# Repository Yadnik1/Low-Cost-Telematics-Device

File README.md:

# Low-Cost Telematics Device for Motor Vehicle Usage-Based Applications

## Overview
This repository details the development of a low-cost telematics device aimed at revolutionizing the motor vehicle insurance sector in India. The device captures critical vehicle kinematics and dynamics data, enabling "pay as you drive" (PAYD) and "pay how you drive" (PHYD) insurance policies. This project addresses the gap in the Indian market for an affordable, after-sales telematics device to assist insurance companies in offering more personalized services.

## Problem Statement
In India, the lack of differentiated underwriting for vehicle insurance fails to consider individual driving patterns and vehicle usage. With over 210 million registered vehicles, the opportunity to tailor insurance policies to driving behavior represents a significant untapped market. This device aims to incentivize safer driving and provide accurate data to support insurance claims and reduce fraud.

## Power Management
The telematics device is powered via a car charger and carefully manages power to support the Raspberry Pi Pico and various sensors. A specialized LDO IC (AZ1117CD) ensures stable voltage for optimal component performance.

#### Power Management Flowchart

## Interfacing Components
Components such as an OLED display, 6DOF IMU, GPS module, and environmental sensors interface with the microcontroller, providing real-time data logging on vehicle behavior and environmental conditions.

#### Interfacing Components Flowchart

#### Components Selection and Planning

## Data Storage
Data is logged onto a micro SD card in CSV format, allowing for extensive data analysis and application in developing insurance models.

# Development

### Documentation and Project Planning
All the project planning was done from ground up and all the documentaion of the project can be seen in the [Documentation folder](Documentation/).

### Component Selection
The component selection for the project was done by benchmarking the STEVAL-STWINKT1B industrial node with the VBOX IMU in real world conditions.
#### Benchmarking setup 

Additional indoor tests were also done by making a setup by laser cutting an acryclic sheet and mounting 5 industrial nodes on it to understand the sensor Systematic Errors and Random Errors in the sensors.

#### Setup to study Variability in sensors

### Designing Breakout boards and Printed Circuit Boards

1) The project involved the use of AECQ100 grade IMU and Temperature and Humidity sensors (SHT30A)  sensors for which custom breakout boards had to be created in KiCAD and hold soldered:
#### Breakout Board PCB of AEC-Q100 compliant SHT-30A Temperature and Humidity Sensor

#### Breakout Board PCB of AEC-Q100 compliant 6-DOF IMU ASM330LHHXTR

#### Fabricated Breakout Boards with IC

2) The PCB of the device was a 2 layered PCB developed using KiCAD consisting of the sensor subsytem on the top layer and power circuitry at the bottom:
#### PCB of Low cost Telematics device

### Developing firmware:

The firmware for the device was written by using the Raspberry Pi Pico as the Microcontroller in C.
The individual C code of the components as well as the entire systems firmware along with the CMake files can be seen in the [Firmware folder](Firmware/).

#### Firmware Development and Validation 

After retreiving the data from the device, errors and noise have to be addressed, for which there is a [seperate repository](https://github.com/Yadnik1/MEMS-IMU-noise-analysis/tree/master) where I have mentioned the different methodologies and filers used in Python for the post-processing process. 

## Usage
To operate the device:
1. Connect to the vehicle's power source.
2. Interact with the OLED display for instructions and status.
3. Retrieve and analyze data from the SD card as needed.

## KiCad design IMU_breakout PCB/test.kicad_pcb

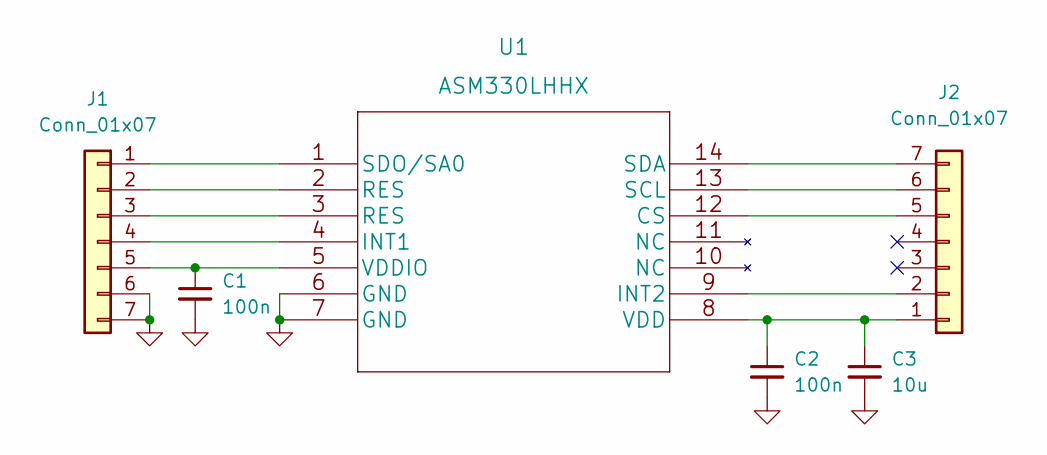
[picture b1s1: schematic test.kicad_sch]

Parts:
C1, C2: 100n; C_0805_2012Metric_Pad1.18x1.45mm_HandSolder
C3: 10u; C_0805_2012Metric_Pad1.18x1.45mm_HandSolder
J1, J2: Conn_01x07; PinHeader_1x07_P2.54mm_Vertical
U1: ASM330LHHX

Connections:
GND: C1.2, C2.2, C3.2, J1.6, J1.7, U1.6 (GND), U1.7 (GND)
unnamed: C2.1, C3.1, J2.1, U1.8 (VDD)
unnamed: J1.1, U1.1 (SDO/SA0)
unnamed: J1.2, U1.2 (RES)
unnamed: J1.3, U1.3 (RES)
unnamed: J1.4, U1.4 (INT1)
unnamed: C1.1, J1.5, U1.5 (VDDIO)
unnamed: J2.2, U1.9 (INT2)
unnamed: J2.5, U1.12 (CS)
unnamed: J2.6, U1.13 (SCL)
unnamed: J2.7, U1.14 (SDA)

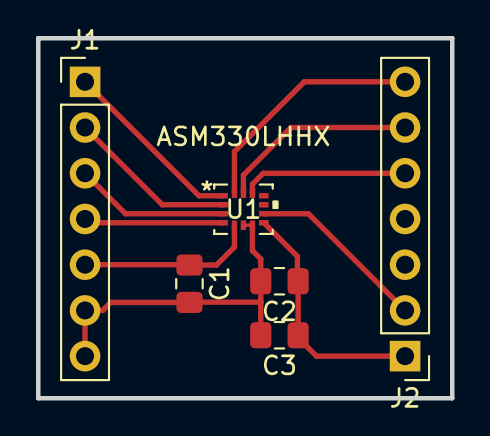
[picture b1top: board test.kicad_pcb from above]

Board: 2 copper layers, 23.0 x 20.0 mm, 6 parts (0 on the bottom side), 11 nets.

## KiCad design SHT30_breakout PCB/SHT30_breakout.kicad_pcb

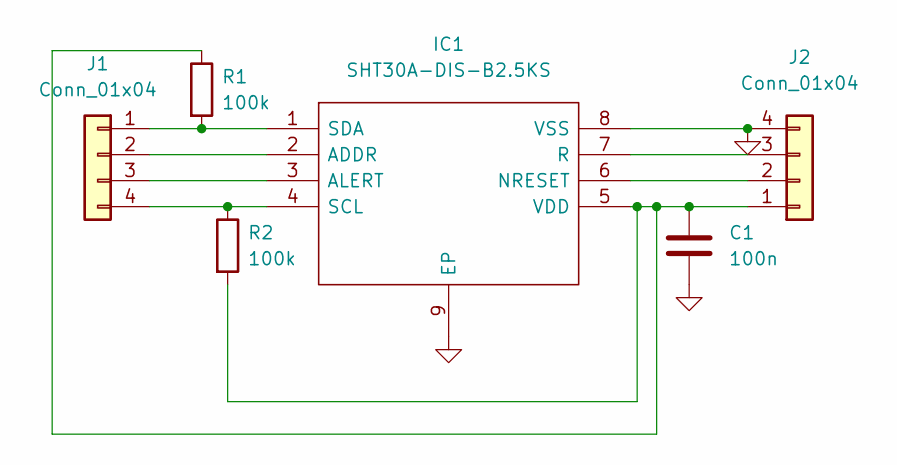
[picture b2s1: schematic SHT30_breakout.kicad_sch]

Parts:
C1: 100n; C_0805_2012Metric_Pad1.18x1.45mm_HandSolder
IC1: SHT30A-DIS-B2.5KS; SON50P250X250X100-9N-D; Manufacturer_Part_Number SHT30A-DIS-B2.5KS; Mouser Part Number 403-SHT30ADIS-B2.5KS
J1, J2: Conn_01x04; PinHeader_1x04_P2.54mm_Vertical
R1, R2: 100k; R_1206_3216Metric_Pad1.30x1.75mm_HandSolder

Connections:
GND: C1.2, IC1.8 (VSS), IC1.9 (EP), J2.4
unnamed: C1.1, IC1.5 (VDD), J2.1, R1.1, R2.2
unnamed: IC1.1 (SDA), J1.1, R1.2
unnamed: IC1.2 (ADDR), J1.2
unnamed: IC1.4 (SCL), J1.4, R2.1
unnamed: IC1.3 (ALERT), J1.3
unnamed: IC1.6 (NRESET), J2.2
unnamed: IC1.7 (R), J2.3

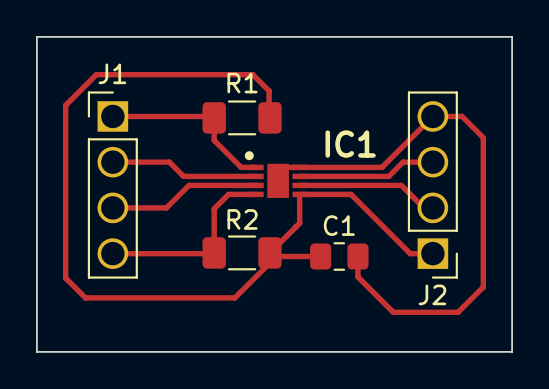
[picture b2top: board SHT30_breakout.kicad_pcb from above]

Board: 2 copper layers, 26.4 x 17.5 mm, 6 parts (0 on the bottom side), 8 nets.

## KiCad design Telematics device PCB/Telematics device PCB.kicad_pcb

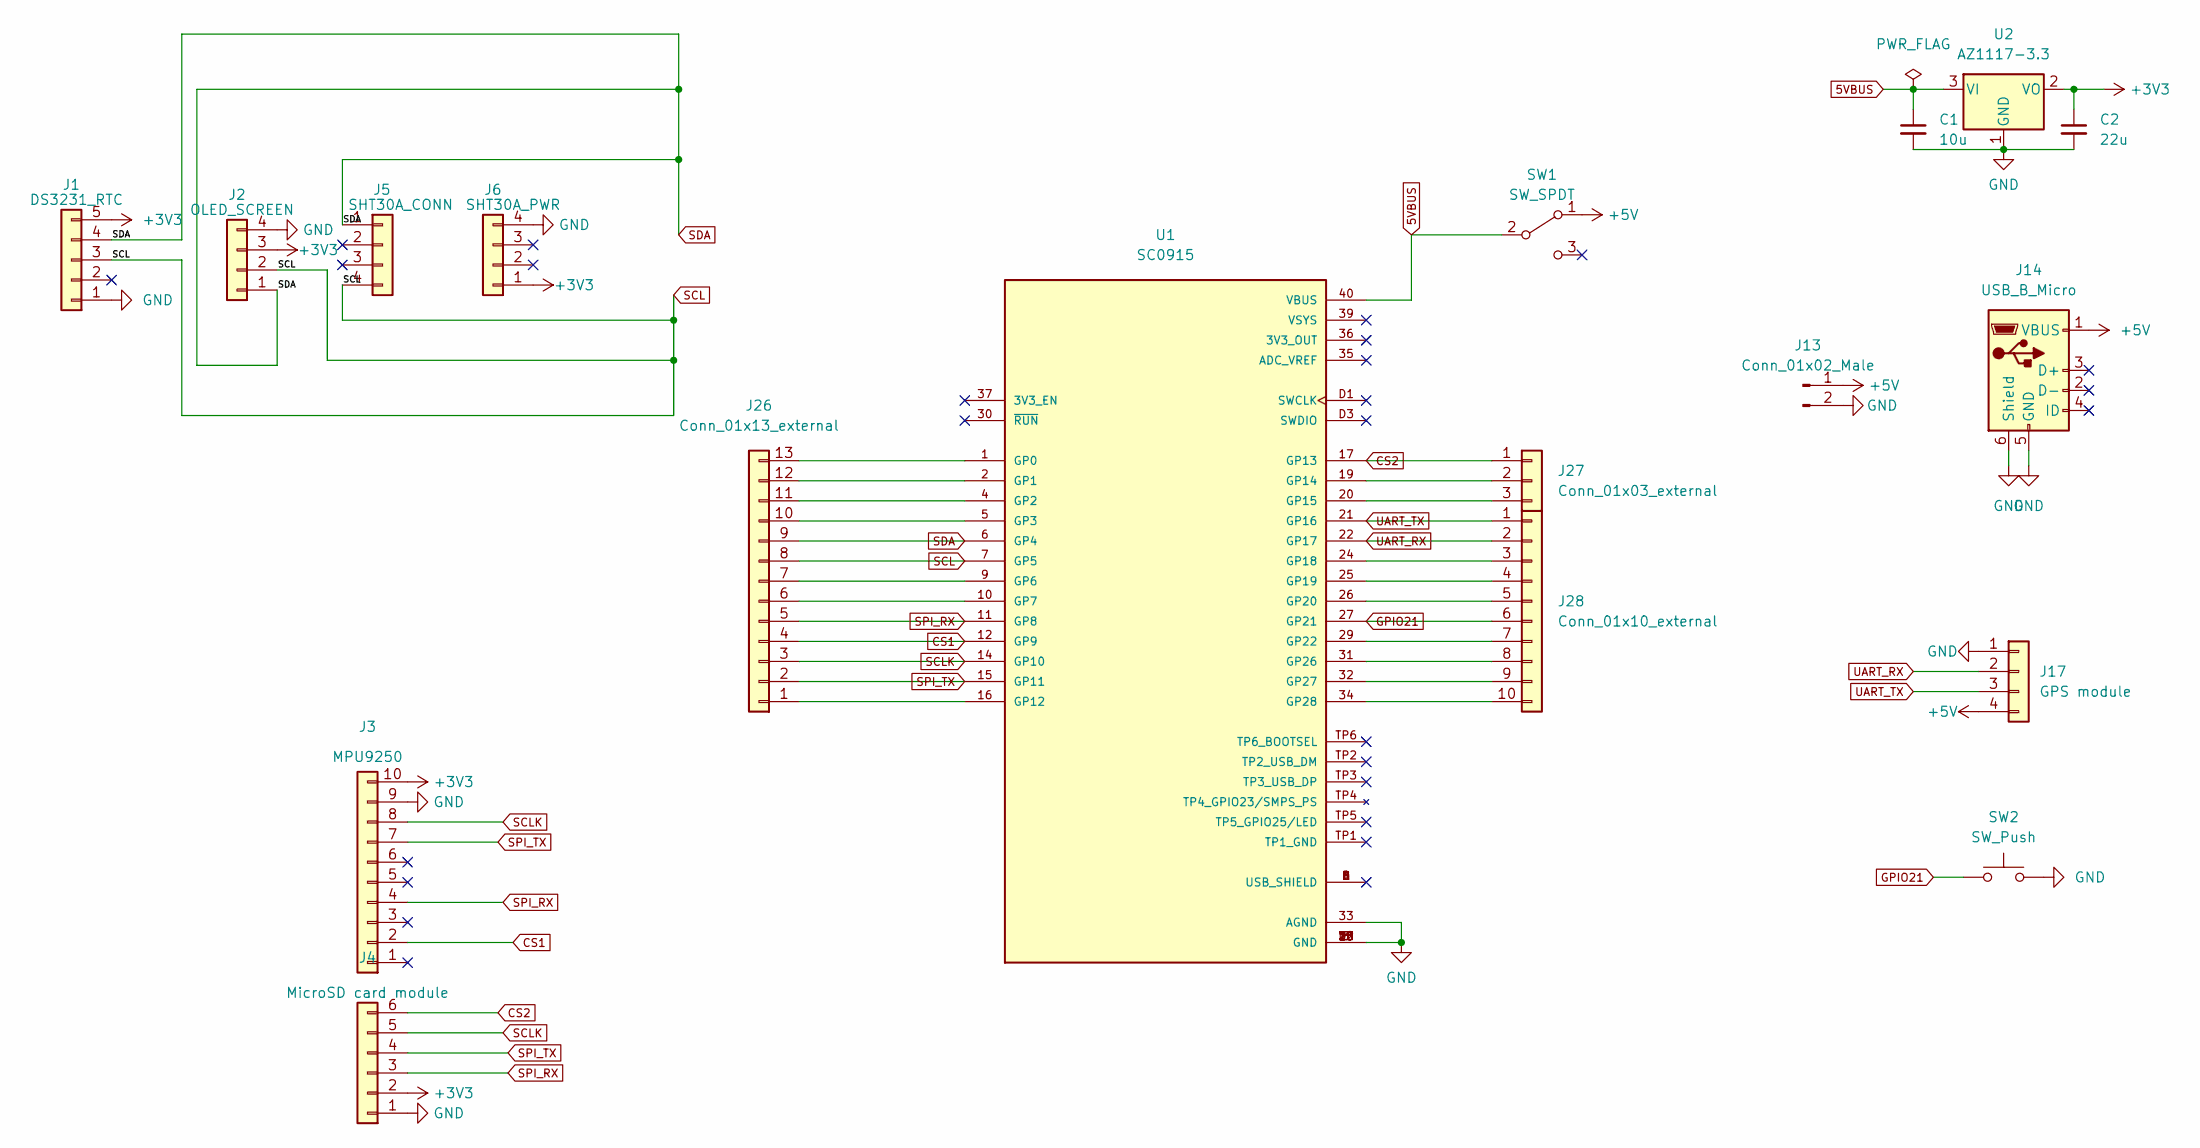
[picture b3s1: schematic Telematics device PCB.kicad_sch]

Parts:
C1: 10u; CP_Radial_D5.0mm_P2.50mm
C2: 22u; CP_Radial_D5.0mm_P2.50mm
J1: DS3231_RTC; PinHeader_1x05_P2.54mm_Vertical
J2: OLED_SCREEN; PinHeader_1x04_P2.54mm_Vertical
J3: MPU9250; PinHeader_1x10_P2.54mm_Vertical
J4: MicroSD card module; PinHeader_1x06_P2.54mm_Vertical
J5: SHT30A_CONN; PinHeader_1x04_P2.54mm_Vertical
J6: SHT30A_PWR; PinHeader_1x04_P2.54mm_Vertical
J13: Conn_01x02_Male; PinHeader_1x02_P2.54mm_Vertical
J14: USB_B_Micro; WE_629105136821
J17: GPS module; PinHeader_1x04_P2.54mm_Vertical
J26: Conn_01x13_external; PinHeader_1x13_P2.54mm_Vertical
J27: Conn_01x03_external; PinHeader_1x03_P2.54mm_Vertical
J28: Conn_01x10_external; PinHeader_1x10_P2.54mm_Vertical
SW1: SW_SPDT; SPDT switch
SW2: SW_Push; Push button
U1: SC0915; MODULE_SC0915; PARTREV 1.6
U2: AZ1117-3.3; DPAK457P1010X238-3N

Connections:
5VBUS: C1.1, SW1.2 (B), U1.40 (VBUS), U2.3 (VI)
+3V3: C2.1, J1.5, J2.3, J3.10, J4.2, J6.1, U2.2 (VO)
+5V: J13.1, J14.1 (VBUS), J17.4, SW1.1 (A)
CS1: J3.2, J26.4, U1.12 (GP9)
CS2: J4.6, J27.1, U1.17 (GP13)
GND: C1.2, C2.2, J1.1, J2.4, J3.9, J4.1, J6.4, J13.2, J14.5 (GND), J14.6 (Shield), J17.1, SW2.2, U1.3 (GND), U1.8 (GND), U1.13 (GND), U1.18 (GND), U1.23 (GND), U1.28 (GND), U1.33 (AGND), U1.38 (GND), U1.D2 (GND), U2.1 (GND)
GPIO21: J28.6, SW2.1, U1.27 (GP21)
unnamed: J26.13, U1.1 (GP0)
unnamed: J26.12, U1.2 (GP1)
unnamed: J26.11, U1.4 (GP2)
unnamed: J26.10, U1.5 (GP3)
unnamed: J26.7, U1.9 (GP6)
unnamed: J26.6, U1.10 (GP7)
unnamed: J26.1, U1.16 (GP12)
unnamed: J27.2, U1.19 (GP14)
unnamed: J27.3, U1.20 (GP15)
unnamed: J28.3, U1.24 (GP18)
unnamed: J28.4, U1.25 (GP19)
unnamed: J28.5, U1.26 (GP20)
unnamed: J28.7, U1.29 (GP22)
unnamed: J28.8, U1.31 (GP26)
unnamed: J28.9, U1.32 (GP27)
unnamed: J28.10, U1.34 (GP28)
SCL: J1.3, J2.2, J5.4, J26.8, U1.7 (GP5)
SCLK: J3.8, J4.5, J26.3, U1.14 (GP10)
SDA: J1.4, J2.1, J5.1, J26.9, U1.6 (GP4)
SPI_RX: J3.4, J4.3, J26.5, U1.11 (GP8)
SPI_TX: J3.7, J4.4, J26.2, U1.15 (GP11)
UART_RX: J17.2, J28.2, U1.22 (GP17)
UART_TX: J17.3, J28.1, U1.21 (GP16)

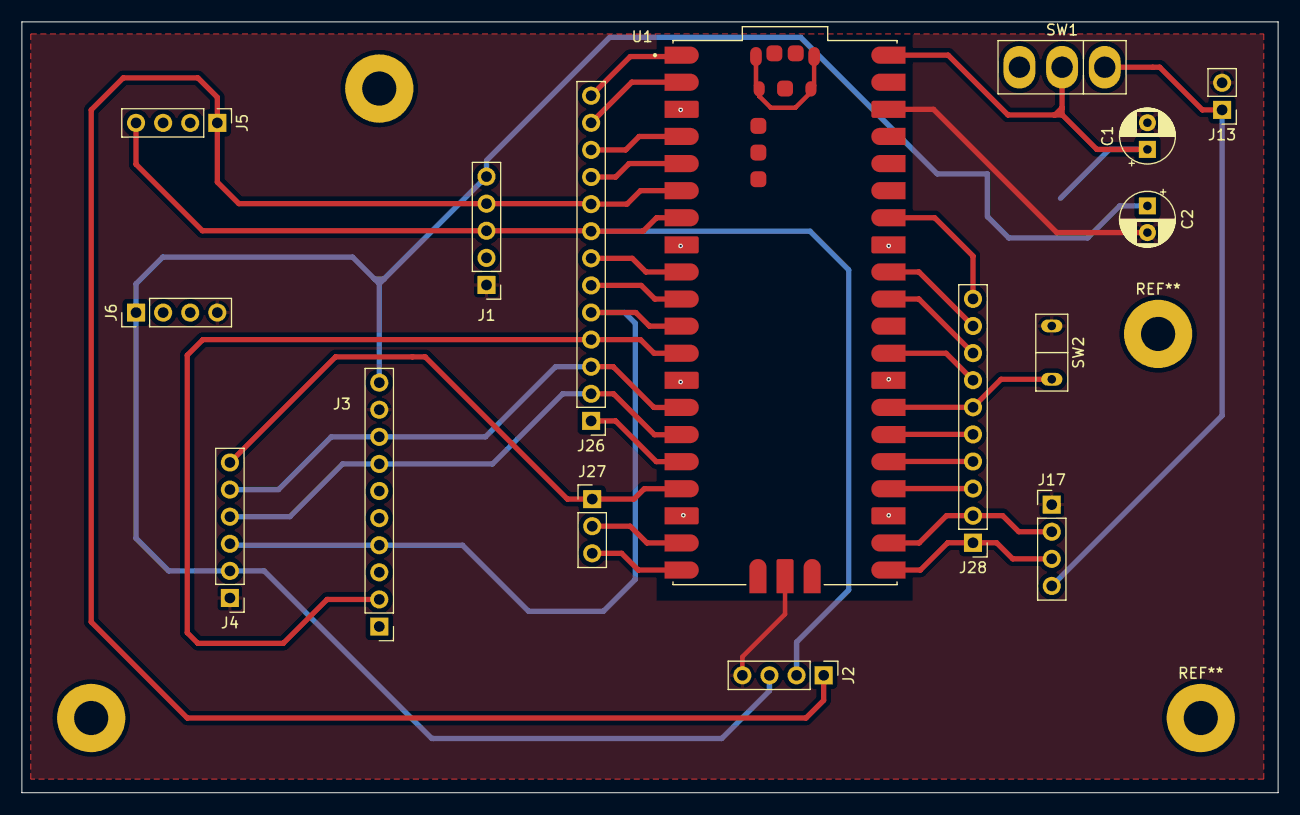
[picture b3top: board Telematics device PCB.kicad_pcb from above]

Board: 2 copper layers, 117.8 x 72.2 mm, 17 parts (1 on the bottom side), 30 nets.

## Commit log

2024-01-08 Create IMU
2024-01-08 Create test
2024-01-08 Updated firmware files

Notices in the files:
parts and their libraries:
Copyright 2021 Accelerated Designs. All rights reserved.
